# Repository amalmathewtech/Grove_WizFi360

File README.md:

# Grove_WizFi360

Grove - UART - WizFi360 is a serial transceiver module featuring the WizNet's WizFi360 WiFi module .With integrated TCP/IP protocol stack, this module lets your micro-controller interact with WiFi networks with only a few lines of code. Each WizFi360 module comes pre-programmed with an AT command set firmware, meaning you can send simple text commands to control the device.
 
Connectivity is provided via 2.4Ghz wireless connection, WizFi360 is compatible with IEEE802.11 b/g/n standards and supports SoftAP, Station and SoftAP+Station modes.

Design Files: This project is designed using Open Source KiCad .Design files are located [here](https://github.com/amalmathewtech/Grove_WizFi360/tree/main/kicad_design_files)

You can download Schematics from [here](https://github.com/amalmathewtech/Grove_WizFi360/tree/main/schematics)

This work is licensed under the MIT License

Made With ❤ in OpenSource

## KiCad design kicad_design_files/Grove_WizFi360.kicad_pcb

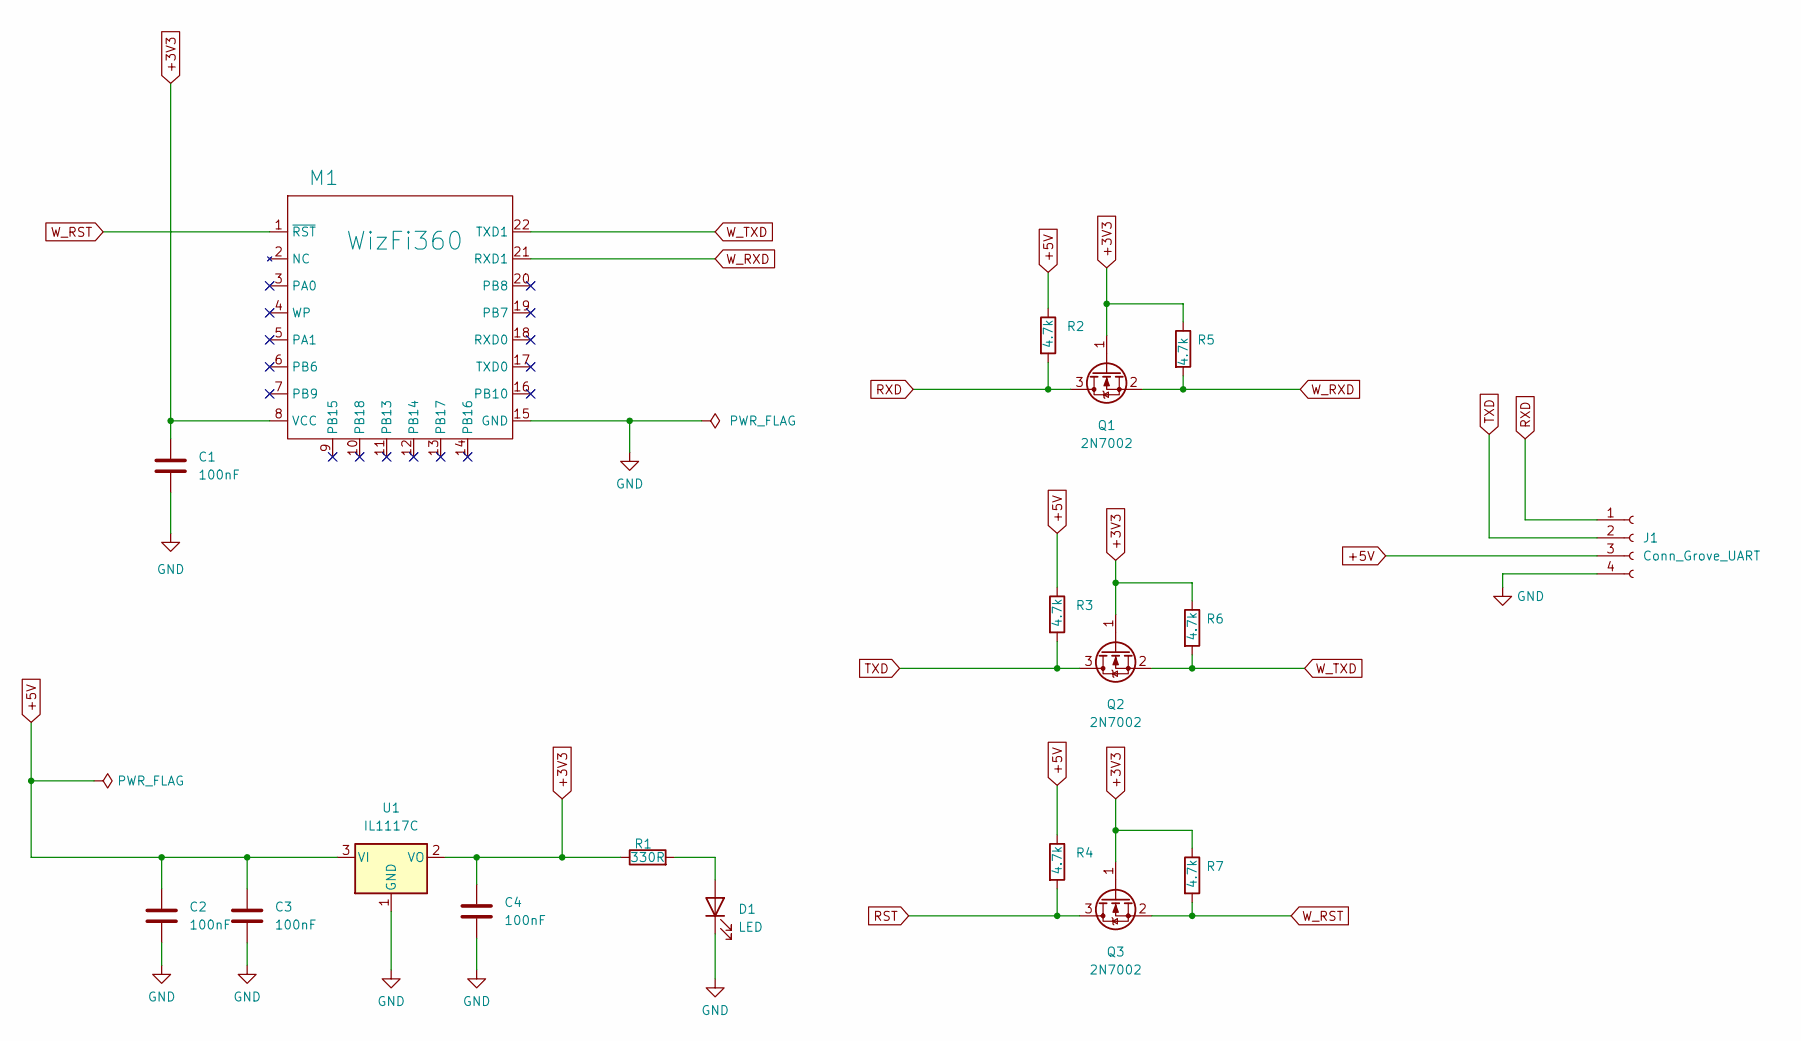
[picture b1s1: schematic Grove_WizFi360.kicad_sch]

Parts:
C1, C2, C3, C4: 100nF; C_0201_0603Metric
D1: LED; LED_0603_1608Metric_Pad1.05x0.95mm_HandSolder
J1: Conn_Grove_UART; PinHeader_1x04_P2.00mm_Vertical
M1: WizFi360; WizFi360-PA
Q1, Q2, Q3: 2N7002; SOT-23
R1: 330R; R_0201_0603Metric_Pad0.64x0.40mm_HandSolder
R2, R3, R4, R5, R6, R7: 4.7k; R_0201_0603Metric_Pad0.64x0.40mm_HandSolder
U1: IL1117C; SOT-223-3_TabPin2

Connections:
+3V3: C1.1, C4.1, M1.8 (VCC), Q1.1 (G), Q2.1 (G), Q3.1 (G), R1.1, R5.1, R6.1, R7.1, U1.2 (VO); also elsewhere on the board
+5V: C2.1, C3.1, J1.3, R2.1, R3.1, R4.1, U1.3 (VI); also elsewhere on the board
GND: C1.2, C2.2, C3.2, C4.2, D1.1 (K), J1.4, M1.15 (GND), U1.1 (GND)
unnamed: D1.2 (A), R1.2
RST: Q3.3 (D), R4.2
RXD: J1.1, Q1.3 (D), R2.2
TXD: J1.2, Q2.3 (D), R3.2
W_RST: M1.1 (~RST), Q3.2 (S), R7.2
W_RXD: M1.21 (RXD1), Q1.2 (S), R5.2
W_TXD: M1.22 (TXD1), Q2.2 (S), R6.2

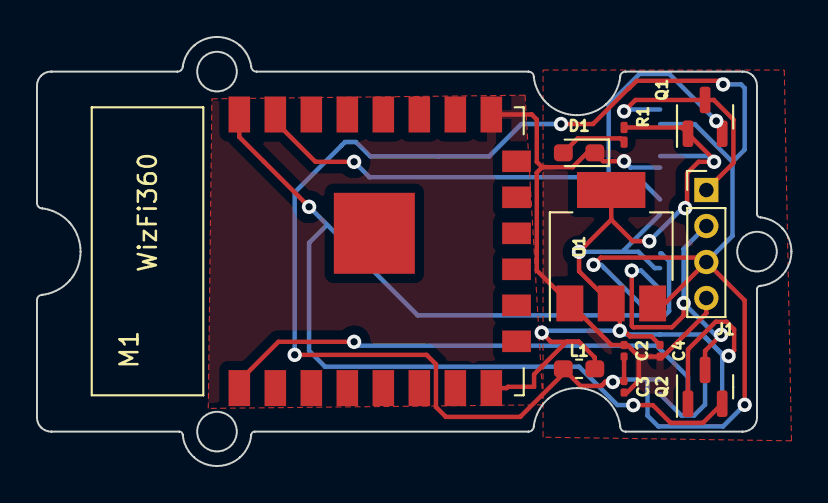
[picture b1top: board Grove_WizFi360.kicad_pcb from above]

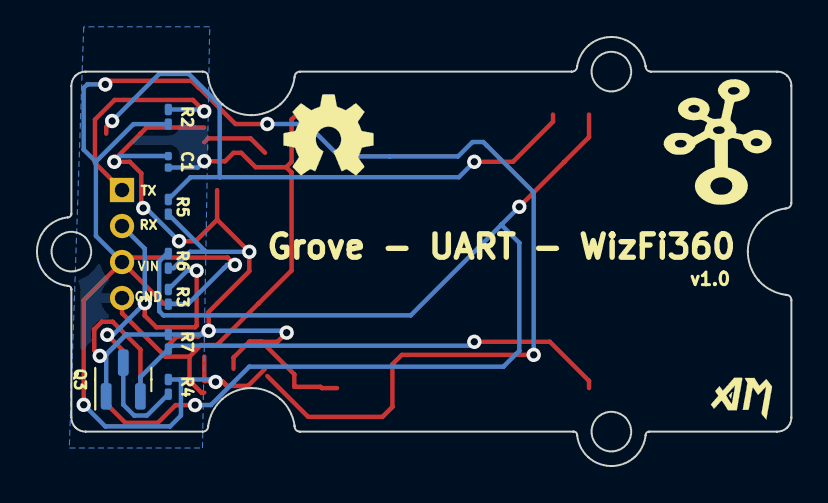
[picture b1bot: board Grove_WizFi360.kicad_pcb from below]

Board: 2 copper layers, 41.9 x 23.8 mm, 20 parts (9 on the bottom side), 10 nets.

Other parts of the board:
***: LOGO; grove_logo
L1: HH-1M1608-; L_0603_1608Metric_Pad1.05x0.95mm_HandSolder

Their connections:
+3V3: L1.2; also elsewhere on the board
+5V: L1.1; also elsewhere on the board

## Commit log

2022-10-29 grove_wizfi360_at_command_test.py file added
    Python code to check AT commands with WizFi360
2022-10-29 added comment about serial port selection
2022-10-29 grove_wizfi360 Testing Process Added
2022-10-29 added test pass and error png image files
2022-10-29 WizFi360_ _Arduino _Library folder added
2022-10-29 arduino example code added

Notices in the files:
kicad_design_files/Grove_WizFi360.kicad_sch:
creativecommons.org/licenses/by/4.0
License: CC BY 4.0
